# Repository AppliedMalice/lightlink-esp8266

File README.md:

# LightLink ESP8266

WiFi replacement controller for the **Inova LightLink CFM16.200** LED sign (1998, 200 x 16 pixels,
red / green / orange). The original controller could only be programmed with expensive proprietary
software. This project replaces it with an ESP8266 that drives the original panel boards directly
and adds a web interface, a playlist, `.fseq` sequence playback, and live control from
Falcon Player (FPP) or xLights.

## Features

- **Web UI** with a live preview of the sign, quick messages, a playlist editor, a file manager and settings
- **Text** in 5 fonts, red / green / orange / cycling color, static / scroll / blink, with
  `{time}` `{time12}` `{date}` `{ip}` `{host}` tokens (NTP time)
- **FSEQ playback** from flash: xLights / FPP V1 or V2-uncompressed sequences
- **Live input** from Falcon Player or xLights over **DDP** (UDP 4048) and **E1.31 / sACN** unicast (UDP 5568)
- **Test patterns** and orientation toggles, so no reflashing to fix a mirrored or swapped display
- WiFi setup access point, mDNS name (`<hostname>.local`), OTA updates, optional HTTP basic auth
- **REST API** for scripts, Home Assistant, chat bots and similar

## Status

Running on a real CFM16.200: both bands, all five panels per band, red, green and orange
all verified.

## Documentation

| Guide | What's in it |
|---|---|
| [Hardware and wiring](docs/hardware.md) | How the panels work, ribbon pinout, parts list, wiring diagram, photos |
| [Building](docs/building.md) | Compiling from source with PlatformIO or the Arduino IDE |
| [Flashing](docs/flashing.md) | Installing esptool (macOS, Linux, Windows) and flashing the prebuilt binary |
| [First-time setup](docs/setup.md) | Joining WiFi, setting the hostname, finding the IP, bring-up tests |
| [Usage](docs/usage.md) | Web UI, messages, playlists, sequences, FPP / xLights, REST API, Home Assistant |
| [Troubleshooting](docs/troubleshooting.md) | Symptoms and fixes, including what a broken data line looks like |
| [Interface PCB](docs/pcb.md) | Through-hole board: PCBWay ordering, BOM, assembly, KiCad files |

## Quick start

1. Build the interface: a Wemos D1 mini or NodeMCU and two 74HCT245 buffers between the ESP8266 and the
   two panel ribbons, either hand-wired ([hardware.md](docs/hardware.md)) or on the
   [interface PCB](docs/pcb.md).
2. Flash [`firmware/lightlink-d1mini-4M3M-v1.0.0.bin`](firmware/) with esptool. See [flashing.md](docs/flashing.md).
3. Join the **LightLink-XXXX** WiFi network (password `lightlink`), browse to `http://192.168.4.1`,
   and enter your WiFi details. See [setup.md](docs/setup.md).
4. Open `http://<hostname>.local`, run **Setup → ident**, then start sending messages.

```
curl -X POST 'http://lightlink.local/api/message?text=Hello%20world&color=green&effect=scroll'
```

## Repository layout

```
src/            firmware source (PlatformIO / Arduino, ESP8266)
firmware/       prebuilt image for a Wemos D1 mini (4 MB flash)
tools/          make_test_fseq.py: generates a test sequence
docs/           guides, wiring diagram and photos
hardware/pcb/   KiCad project, Gerbers for PCBWay, BOM for the interface board
.github/        CI workflow that builds the firmware on every push
```

## Credits

- The panel interface (signal list, ribbon pinout, row addressing) comes from **Yadid Ramot's**
  PIC24 + ESP8266 replacement controller for LightLink signs:
  [hackaday.io/project/8365](https://hackaday.io/project/8365) and
  [github.com/eyadid/esp-led-controller](https://github.com/eyadid/esp-led-controller).
- Built with the [ESP8266 Arduino core](https://github.com/esp8266/Arduino),
  [Adafruit GFX](https://github.com/adafruit/Adafruit-GFX-Library) and
  [ArduinoJson](https://arduinojson.org/).
- FSEQ format per [Falcon Player](https://github.com/FalconChristmas/fpp); DDP per [3waylabs](http://www.3waylabs.com/ddp/).

## License

MIT. See [LICENSE](LICENSE).

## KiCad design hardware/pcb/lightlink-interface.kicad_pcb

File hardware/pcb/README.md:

# LightLink ESP8266 interface PCB (rev 1.0)

- **Order:** upload `lightlink-interface-gerbers-pcbway.zip` to PCBWay (2 layers, 1.6 mm, 1 oz, HASL).
- **Parts:** `bom.csv`
- **Everything else** (ordering options, assembly, jumper use, editing in KiCad on a Mac):
  [docs/pcb.md](../../docs/pcb.md)

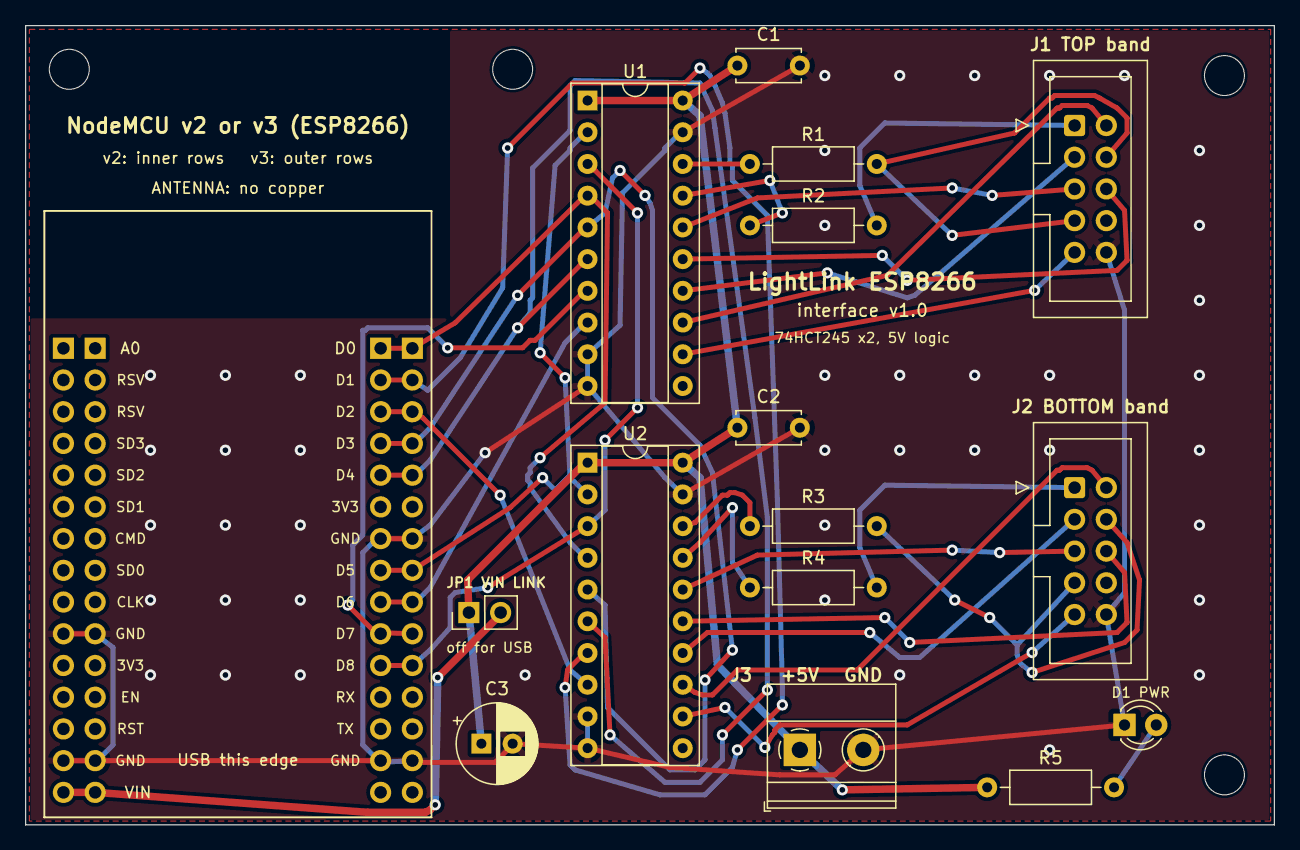
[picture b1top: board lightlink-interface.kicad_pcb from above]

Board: 2 copper layers, 100.0 x 64.0 mm, 23 parts (0 on the bottom side), 31 nets.

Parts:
C1, C2: 100nF; C_Disc_D5.0mm_W2.5mm_P5.00mm
C3: 100uF; CP_Radial_D6.3mm_P2.50mm
D1: PWR; LED_D3.0mm
H1, H2, H3, H4: M3; MountingHole_3.2mm_M3
J1: TOP band ribbon; IDC-Header_2x05_P2.54mm_Vertical
J2: BOTTOM band ribbon; IDC-Header_2x05_P2.54mm_Vertical
J3: 5V IN; TerminalBlock_Phoenix_MKDS-1,5-2-5.08_1x02_P5.08mm_Horizont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
JP1: VIN link; PinHeader_1x02_P2.54mm_Vertical
MCU_L2: NodeMCU v2 Amica; PinHeader_1x15_P2.54mm_Vertical
MCU_L3: NodeMCU v3 LoLin; PinHeader_1x15_P2.54mm_Vertical
MCU_R2: NodeMCU v2 Amica; PinHeader_1x15_P2.54mm_Vertical
MCU_R3: NodeMCU v3 LoLin; PinHeader_1x15_P2.54mm_Vertical
R1, R2, R3, R4: 33R; R_Axial_DIN0207_L6.3mm_D2.5mm_P10.16mm_Horizontal
R5: 1k; R_Axial_DIN0207_L6.3mm_D2.5mm_P10.16mm_Horizontal
U1, U2: 74HCT245; DIP-20_W7.62mm_Socket

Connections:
+5V: C1.1, C2.1, C3.1, J3.1, JP1.1, R5.1, U1.1, U1.20, U2.1, U2.20
BOT_GREEN: J2.9, U2.12
BOT_RCK: J2.1, R4.2
BOT_RCK_U: R4.1, U2.17
BOT_RED: J2.2, U2.13
BOT_ROW_A: J2.5, U2.16
BOT_ROW_B: J2.6, U2.15
BOT_ROW_C: J2.3, U2.14
BOT_SRCK: J2.4, J2.7, R3.2
BOT_SRCK_U: R3.1, U2.18
D0: MCU_R2.1, MCU_R3.1, U1.4, U2.4
D1: MCU_R2.2, MCU_R3.2, U2.7
D2: MCU_R2.3, MCU_R3.3, U2.8
D3: MCU_R2.4, MCU_R3.4, U1.5, U2.5
D4: MCU_R2.5, MCU_R3.5, U1.6, U2.6
D5: MCU_R2.8, MCU_R3.8, U1.2, U2.2
D6: MCU_R2.9, MCU_R3.9, U1.8
D7: MCU_R2.10, MCU_R3.10, U1.7
D8: MCU_R2.11, MCU_R3.11, U1.3, U2.3
GND: C1.2, C2.2, C3.2, D1.1, J1.10, J2.10, J3.2, MCU_L2.10, MCU_L2.14, MCU_L3.10, MCU_L3.14, MCU_R2.7, MCU_R2.14, MCU_R3.7, MCU_R3.14, U1.9, U1.10, U1.19, U2.9, U2.10, U2.19
LED_A: D1.2, R5.2
TOP_GREEN: J1.9, U1.12
TOP_RCK: J1.1, R2.2
TOP_RCK_U: R2.1, U1.17
TOP_RED: J1.2, U1.13
TOP_ROW_A: J1.5, U1.16
TOP_ROW_B: J1.6, U1.15
TOP_ROW_C: J1.3, U1.14
TOP_SRCK: J1.4, J1.7, R1.2
TOP_SRCK_U: R1.1, U1.18
VIN: JP1.2, MCU_L2.15, MCU_L3.15

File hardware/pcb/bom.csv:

Ref,Qty,Value,Description,Footprint,Notes
U1 U2,2,74HCT245,Octal bus transceiver DIP-20 (must be HCT/AHCT/ACT),DIP-20 0.3in,Notch toward the top edge (pin 1 = square pad)
(sockets),2,DIP-20 socket,IC socket DIP-20 0.3in,DIP-20,Recommended
J1 J2,2,2x5 box header,Shrouded IDC header 2.54mm straight,IDC-Header_2x05_P2.54mm_Vertical,Takes the original LightLink ribbons; notch faces the board centre
J3,1,2-pos 5.08mm,PCB screw terminal 5.08mm pitch (KF301 / MKDS style),TerminalBlock 1x02 P5.08mm,Wire entry faces the bottom edge; left = +5V
JP1,1,1x2 header + shunt,2.54mm pin header with jumper,PinHeader_1x02_P2.54mm,VIN link
R1 R2 R3 R4,4,33R,Resistor 1/4 W axial (22-100R works),Axial 10.16mm,Series damping SRCK/RCK
R5,1,1k,Resistor 1/4 W axial,Axial 10.16mm,LED current
C1 C2,2,100nF,Ceramic capacitor (code 104) 5.0/5.08mm lead pitch,C_Disc P5.00mm,Decoupling at each 74HCT245
C3,1,100uF 10V+,Electrolytic radial 2.5mm pitch <=6.3mm dia,CP_Radial_D6.3mm_P2.50mm,Square pad = +
D1,1,LED 3mm,Any colour,LED_D3.0mm,Square pad = cathode (flat side / short leg)
MCU,1,NodeMCU v2 or v3,ESP8266 NodeMCU with pins,Dual 1x15 rows,v2 inner rows / v3 outer rows; antenna toward the top edge
H1-H4,4,M3,Mounting holes 3.2mm (optional standoffs),MountingHole_3.2mm_M3,
